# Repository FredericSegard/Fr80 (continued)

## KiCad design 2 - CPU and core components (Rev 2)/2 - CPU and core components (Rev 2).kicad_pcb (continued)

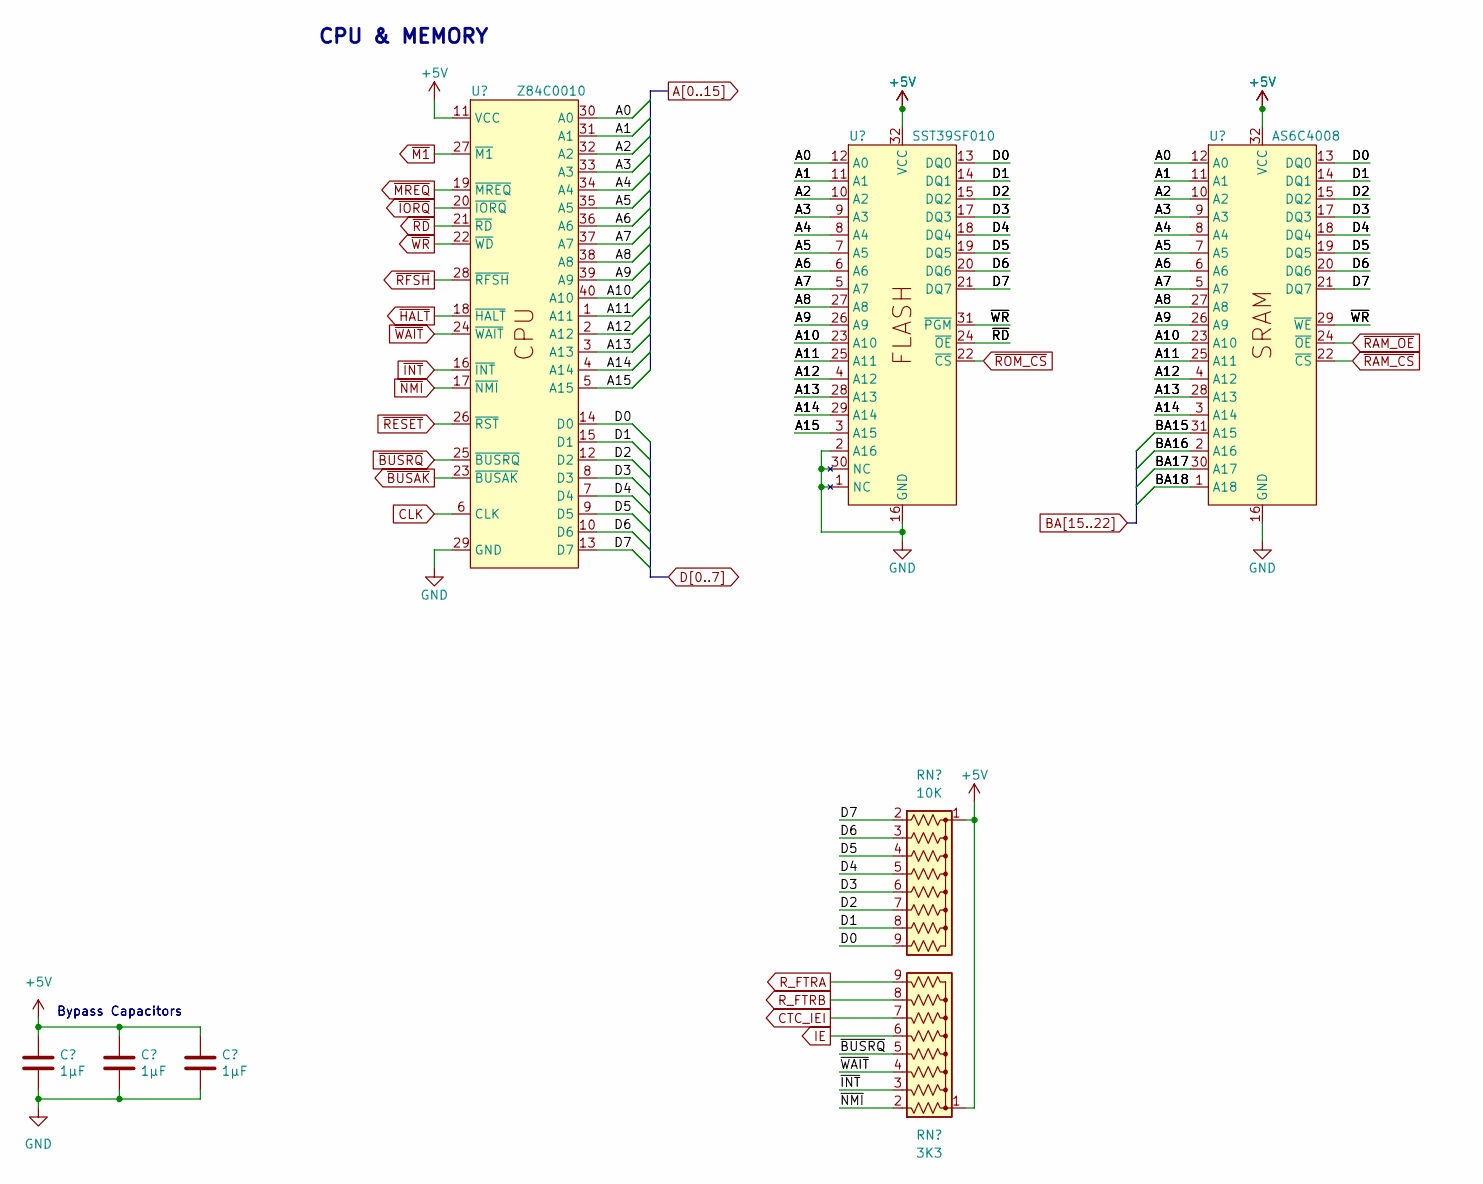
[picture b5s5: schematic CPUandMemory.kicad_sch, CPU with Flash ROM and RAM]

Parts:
C11, C12, C13: 1µF; C_Disc_D3.4mm_W2.1mm_P2.50mm
RN3: 10K; R_Array_SIP9
RN4: 3K3; R_Array_SIP9
U10: Z84C0010; DIP-40_W15.24mm_Socket
U11: SST39SF010; ZIF_Socket-32
U12: AS6C4008; DIP-32_W15.24mm_Socket

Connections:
+5V: C11.1, C12.1, C13.1, RN3.1 (common), RN4.1 (common), U10.11 (VCC), U11.32 (VCC), U12.32 (VCC); also elsewhere on the board
A0: U10.30 (A0), U11.12 (A0), U12.12 (A0); also elsewhere on the board
A1: U10.31 (A1), U11.11 (A1), U12.11 (A1); also elsewhere on the board
A2: U10.32 (A2), U11.10 (A2), U12.10 (A2); also elsewhere on the board
A3: U10.33 (A3), U11.9 (A3), U12.9 (A3); also elsewhere on the board
A4: U10.34 (A4), U11.8 (A4), U12.8 (A4); also elsewhere on the board
A5: U10.35 (A5), U11.7 (A5), U12.7 (A5); also elsewhere on the board
A6: U10.36 (A6), U11.6 (A6), U12.6 (A6); also elsewhere on the board
A7: U10.37 (A7), U11.5 (A7), U12.5 (A7); also elsewhere on the board
A8: U10.38 (A8), U11.27 (A8), U12.27 (A8); also elsewhere on the board
A9: U10.39 (A9), U11.26 (A9), U12.26 (A9); also elsewhere on the board
A10: U10.40 (A10), U11.23 (A10), U12.23 (A10); also elsewhere on the board
A11: U10.1 (A11), U11.25 (A11), U12.25 (A11); also elsewhere on the board
A12: U10.2 (A12), U11.4 (A12), U12.4 (A12); also elsewhere on the board
A13: U10.3 (A13), U11.28 (A13), U12.28 (A13); also elsewhere on the board
A14: U10.4 (A14), U11.29 (A14), U12.3 (A14); also elsewhere on the board
A15: U10.5 (A15), U11.3 (A15); also elsewhere on the board
BA15: U12.31 (A15); also elsewhere on the board
BA16: U12.2 (A16); also elsewhere on the board
BA17: U12.30 (A17); also elsewhere on the board
BA18: U12.1 (A18); also elsewhere on the board
CLK: U10.6 (CLK); also elsewhere on the board
CTC_IEI: RN4.7 (R6); also elsewhere on the board
D0: RN3.9 (R8), U10.14 (D0), U11.13 (DQ0), U12.13 (DQ0); also elsewhere on the board
D1: RN3.8 (R7), U10.15 (D1), U11.14 (DQ1), U12.14 (DQ1); also elsewhere on the board
D2: RN3.7 (R6), U10.12 (D2), U11.15 (DQ2), U12.15 (DQ2); also elsewhere on the board
D3: RN3.6 (R5), U10.8 (D3), U11.17 (DQ3), U12.17 (DQ3); also elsewhere on the board
D4: RN3.5 (R4), U10.7 (D4), U11.18 (DQ4), U12.18 (DQ4); also elsewhere on the board
D5: RN3.4 (R3), U10.9 (D5), U11.19 (DQ5), U12.19 (DQ5); also elsewhere on the board
D6: RN3.3 (R2), U10.10 (D6), U11.20 (DQ6), U12.20 (DQ6); also elsewhere on the board
D7: RN3.2 (R1), U10.13 (D7), U11.21 (DQ7), U12.21 (DQ7); also elsewhere on the board
GND: C11.2, C12.2, C13.2, U10.29 (GND), U11.1 (NC), U11.2 (A16), U11.16 (GND), U11.30 (NC), U12.16 (GND); also elsewhere on the board
IE: RN4.6 (R5); also elsewhere on the board
R_FTRA: RN4.9 (R8); also elsewhere on the board
R_FTRB: RN4.8 (R7); also elsewhere on the board
~BUSAK: U10.23 (~BUSAK); also elsewhere on the board
~BUSRQ: RN4.5 (R4), U10.25 (~BUSRQ); also elsewhere on the board
~HALT: U10.18 (~HALT); also elsewhere on the board
~INT: RN4.3 (R2), U10.16 (~INT); also elsewhere on the board
~IORQ: U10.20 (~IORQ); also elsewhere on the board
~M1: U10.27 (~M1); also elsewhere on the board
~MREQ: U10.19 (~MREQ); also elsewhere on the board
~NMI: RN4.2 (R1), U10.17 (~NMI); also elsewhere on the board
~RAM_CS: U12.22 (~CS); also elsewhere on the board
~RAM_OE: U12.24 (~OE); also elsewhere on the board
~RD: U10.21 (~RD), U11.24 (~OE); also elsewhere on the board
~RESET: U10.26 (~RST); also elsewhere on the board
~RFSH: U10.28 (~RFSH); also elsewhere on the board
~ROM_CS: U11.22 (~CS); also elsewhere on the board
~WAIT: RN4.4 (R3), U10.24 (~WAIT); also elsewhere on the board
~WR: U10.22 (~WD), U11.31 (~PGM), U12.29 (~WE); also elsewhere on the board

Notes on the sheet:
Bypass Capacitors
CPU & MEMORY

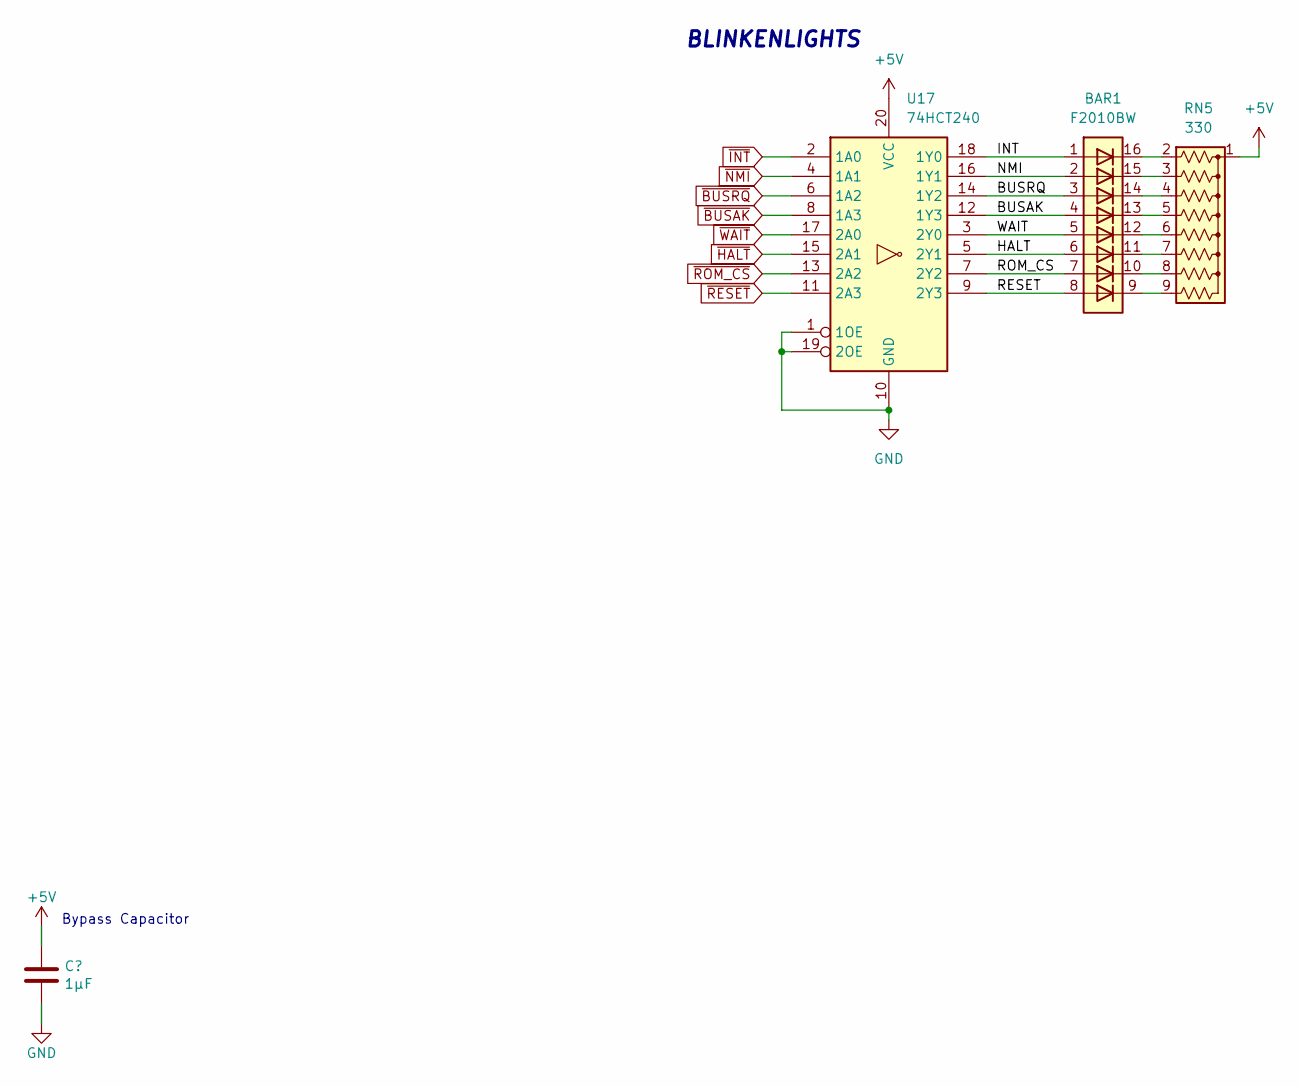
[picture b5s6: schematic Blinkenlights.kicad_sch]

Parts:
BAR1: F2010BW; BAR_GRAPH_8
C14: 1µF; C_Disc_D3.4mm_W2.1mm_P2.50mm
RN5: 330; R_Array_SIP9
U17: 74HCT240; DIP-20_W7.62mm_Socket

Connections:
+5V: C14.1, RN5.1 (common), U17.20 (VCC); also elsewhere on the board
/Blinkenlights/BUSAK: BAR1.4 (A), U17.12 (1Y3)
/Blinkenlights/BUSRQ: BAR1.3 (A), U17.14 (1Y2)
/Blinkenlights/HALT: BAR1.6 (A), U17.5 (2Y1)
/Blinkenlights/INT: BAR1.1 (A), U17.18 (1Y0)
/Blinkenlights/NMI: BAR1.2 (A), U17.16 (1Y1)
/Blinkenlights/RESET: BAR1.8 (A), U17.9 (2Y3)
/Blinkenlights/ROM_CS: BAR1.7 (A), U17.7 (2Y2)
/Blinkenlights/WAIT: BAR1.5 (A), U17.3 (2Y0)
GND: C14.2, U17.1 (1OE), U17.10 (GND), U17.19 (2OE); also elsewhere on the board
unnamed: BAR1.16 (K), RN5.2 (R1)
unnamed: BAR1.15 (K), RN5.3 (R2)
unnamed: BAR1.14 (K), RN5.4 (R3)
unnamed: BAR1.13 (K), RN5.5 (R4)
unnamed: BAR1.12 (K), RN5.6 (R5)
unnamed: BAR1.11 (K), RN5.7 (R6)
unnamed: BAR1.10 (A), RN5.8 (R7)
unnamed: BAR1.9 (A), RN5.9 (R8)
~BUSAK: U17.8 (1A3); also elsewhere on the board
~BUSRQ: U17.6 (1A2); also elsewhere on the board
~HALT: U17.15 (2A1); also elsewhere on the board
~INT: U17.2 (1A0); also elsewhere on the board
~NMI: U17.4 (1A1); also elsewhere on the board
~RESET: U17.11 (2A3); also elsewhere on the board
~ROM_CS: U17.13 (2A2); also elsewhere on the board
~WAIT: U17.17 (2A0); also elsewhere on the board

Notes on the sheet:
BLINKENLIGHTS
Bypass Capacitor

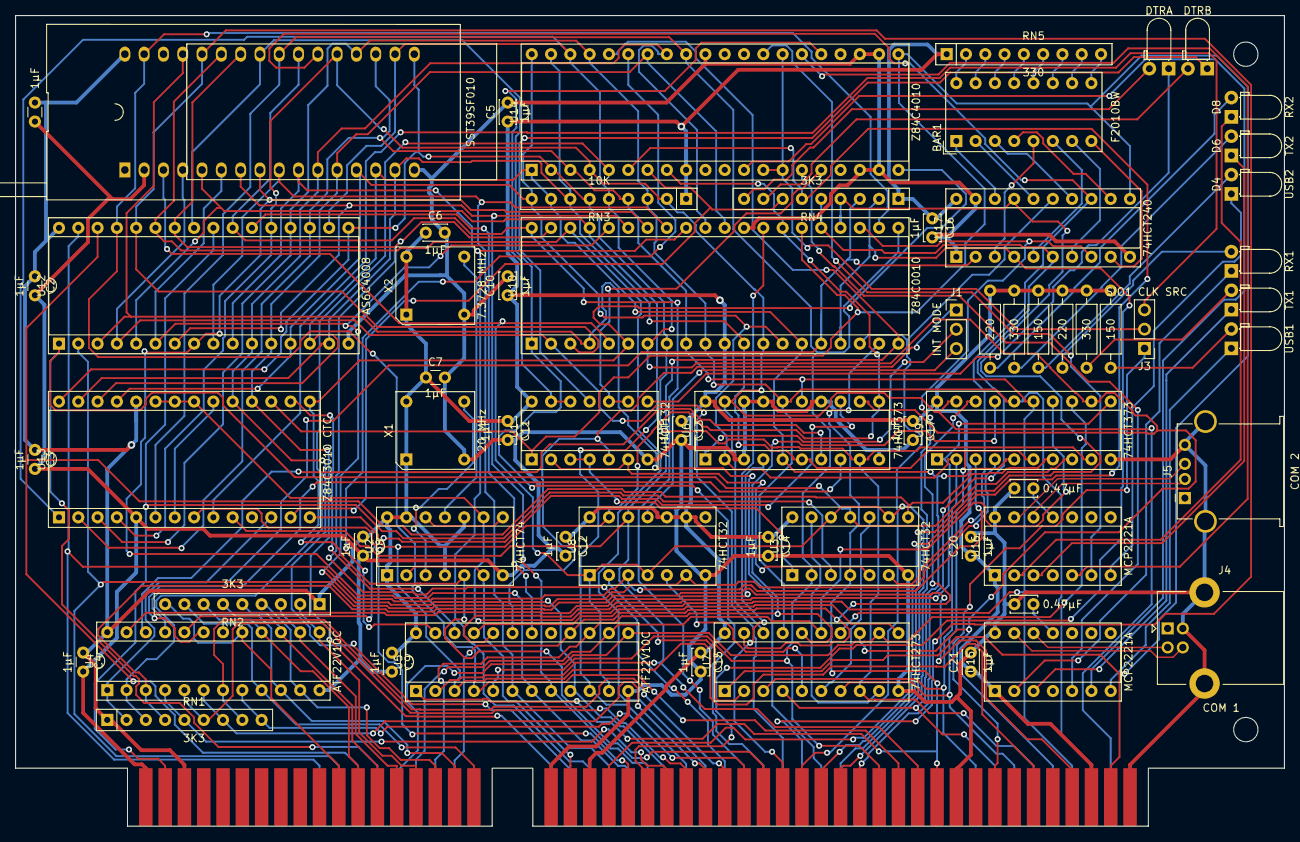
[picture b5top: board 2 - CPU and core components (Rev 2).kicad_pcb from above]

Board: 2 copper layers, 167.0 x 106.7 mm, 65 parts (0 on the bottom side), 139 nets.

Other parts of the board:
C10: 1µF; C_Disc_D3.4mm_W2.1mm_P2.50mm

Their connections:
+5V: C10.1; also elsewhere on the board
GND: C10.2; also elsewhere on the board

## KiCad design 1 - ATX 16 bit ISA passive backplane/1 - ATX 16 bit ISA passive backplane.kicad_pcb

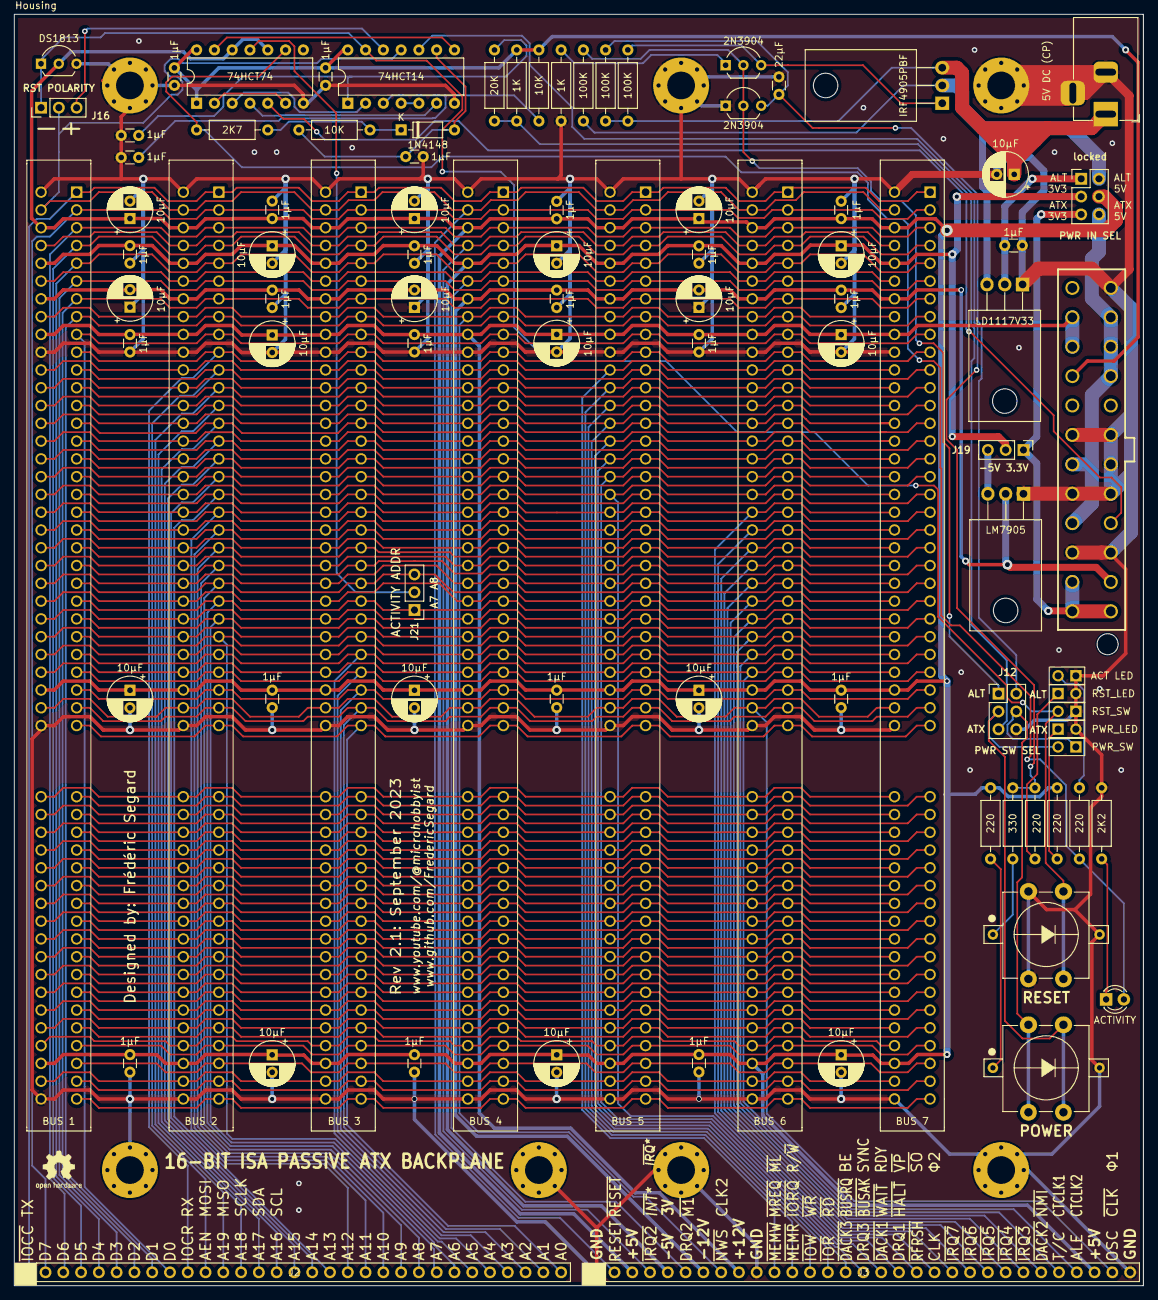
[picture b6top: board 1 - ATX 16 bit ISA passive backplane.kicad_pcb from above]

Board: 2 copper layers, 161.3 x 181.6 mm, 102 parts (1 on the bottom side), 128 nets.

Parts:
C1, C2, C3, C4, C6, C8, C9, C10, C11, C13, C14, C15, C19, C24, C29, C31, C33, C35, C37: 10µF; CP_Radial_D6.3mm_P2.50mm
C5, C7, C12, C16, C17, C18, C20, C21, C22, C23, C25, C26, C27, C28, C30, C32, C34, C36, C38, C39, C42, C44, C45, C46: 1µF; C_Disc_D3.0mm_W1.6mm_P2.50mm
C41: 22µF; C_Disc_D3.0mm_W1.6mm_P2.50mm
D2: 1N4148; D_DO-35_SOD27_P7.62mm_Horizontal
D3: ACTIVITY; LED_D3.0mm
H1, H2, H3, H4, H5, H6, H7: MH; MountingHole_M3.96_Pad_Via_ATX
J1: BUS 1; ISA_Connector_98
J2: A: Component Side; PinHeader_1x31_P2.54mm_Vertical
J3: B: Back Side; PinHeader_1x31_P2.54mm_Vertical
J4: BUS 2; ISA_Connector_98
J5: BUS 3; ISA_Connector_98
J6: BUS 4; ISA_Connector_98
J7: BUS 5; ISA_Connector_98
J8: BUS 6; ISA_Connector_98
J9: BUS 7; ISA_Connector_98
J10: ATX POWER; ATX_PSU_CONN
J12: PWR SW SEL; PinHeader_2x03_P2.54mm_Vertical
J13: PWR_LED; PinHeader_1x2_Vertical (Modified)
J14: PWR_SW; PinHeader_1x2_Vertical (Modified)
J15: 5V DC (CP); BarrelJack_Horizontal
J16: RST POLARITY; PinHeader_1x03_P2.54mm_Vertical
J17: RST_LED; PinHeader_1x2_Vertical (Modified)
J18: RST_SW; PinHeader_1x2_Vertical (Modified)
J19: 3V/-5V; PinHeader_1x03_P2.54mm_Vertical
J20: ACT LED; PinHeader_1x2_Vertical (Modified)
J21: ACTIVITY ADDR; PinHeader_1x03_P2.54mm_Vertical
LOGO1, LOGO2: Logo_Open_Hardware_Small; OSHW-Logo2_7.3x6mm_SilkScreen
N1: Housing; ATX_Backplane
Q1: IRF4905PBF; TO-220-3_Horizontal_TabDown
Q2, Q3: 2N3904; TO-92_Inline_Wide
R1, R2, R11, R17: 220; R_Axial_DIN0207_L6.3mm_D2.5mm_P10.16mm_Horizontal
R3, R6, R7: 100K; R_Axial_DIN0207_L6.3mm_D2.5mm_P10.16mm_Horizontal
R4, R14: 10K; R_Axial_DIN0207_L6.3mm_D2.5mm_P10.16mm_Horizontal
R5, R8: 1K; R_Axial_DIN0207_L6.3mm_D2.5mm_P10.16mm_Horizontal
R9: 20K; R_Axial_DIN0207_L6.3mm_D2.5mm_P10.16mm_Horizontal
R10: 330; R_Axial_DIN0207_L6.3mm_D2.5mm_P10.16mm_Horizontal
R15: 2K7; R_Axial_DIN0207_L6.3mm_D2.5mm_P10.16mm_Horizontal
R16: 2K2; R_Axial_DIN0207_L6.3mm_D2.5mm_P10.16mm_Horizontal
RS1: DS1813; TO-92L_Inline_Wide
SW1: POWER; Pushbutton_12mm_LED
SW2: RESET; Pushbutton_12mm_LED
U1: 74HCT14; DIP-14_W7.62mm
U2: LD1117V33; TO-220-3_Horizontal_TabDown
U3: 74HCT74; DIP-14_W7.62mm
U4: LM7905; TO-220-3_Horizontal_TabDown
locked: PWR IN SEL; PinHeader_2x03_P2.54mm_Vertical

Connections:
+3V3: C4.1, C5.1, C6.1, C7.1, C11.1, C12.1, J1.36 (B5), J3.5, J4.36 (B5), J5.36 (B5), J6.36 (B5), J7.36 (B5), J8.36 (B5), J9.36 (B5), J19.2, locked.3
+5V: C1.1, C2.1, C3.1, C8.1, C9.1, C10.1, C13.1, C14.1, C15.1, C16.1, C17.1, C18.1, C21.1, C22.1, C23.1, C26.1, C27.1, C28.1, J1.34 (B3), J1.60 (B29), J1.96 (D16), J3.3, J3.29, J4.34 (B3), J4.60 (B29), J4.96 (D16), J5.34 (B3), J5.60 (B29), J5.96 (D16), J6.34 (B3), J6.60 (B29), J6.96 (D16), J7.34 (B3), J7.60 (B29), J7.96 (D16), J8.34 (B3), J8.60 (B29), J8.96 (D16), J9.34 (B3), J9.60 (B29), J9.96 (D16), R1.2, R2.2, RS1.2 (VCC), U3.10 (~S), U3.12 (D), locked.4
+12V: C19.1, C20.1, C24.1, C25.1, C29.1, C30.1, J1.40 (B9), J3.9, J4.40 (B9), J5.40 (B9), J6.40 (B9), J7.40 (B9), J8.40 (B9), J9.40 (B9), J10.10 (+12V), J10.11 (+12V)
-12V: C31.2, C32.1, C33.2, C34.1, C35.2, C36.1, J1.38 (B7), J3.7, J4.38 (B7), J5.38 (B7), J6.38 (B7), J7.38 (B7), J8.38 (B7), J9.38 (B7), J10.14 (-12V), U4.2 (VI)
/A0: J1.31 (A31), J2.31, J4.31 (A31), J5.31 (A31), J6.31 (A31), J7.31 (A31), J8.31 (A31), J9.31 (A31)
/A1: J1.30 (A30), J2.30, J4.30 (A30), J5.30 (A30), J6.30 (A30), J7.30 (A30), J8.30 (A30), J9.30 (A30)
/A2: J1.29 (A29), J2.29, J4.29 (A29), J5.29 (A29), J6.29 (A29), J7.29 (A29), J8.29 (A29), J9.29 (A29)
/A3: J1.28 (A28), J2.28, J4.28 (A28), J5.28 (A28), J6.28 (A28), J7.28 (A28), J8.28 (A28), J9.28 (A28)
/A4: J1.27 (A27), J2.27, J4.27 (A27), J5.27 (A27), J6.27 (A27), J7.27 (A27), J8.27 (A27), J9.27 (A27)
/A5: J1.26 (A26), J2.26, J4.26 (A26), J5.26 (A26), J6.26 (A26), J7.26 (A26), J8.26 (A26), J9.26 (A26)
/A6: J1.25 (A25), J2.25, J4.25 (A25), J5.25 (A25), J6.25 (A25), J7.25 (A25), J8.25 (A25), J9.25 (A25)
/A7: J1.24 (A24), J2.24, J4.24 (A24), J5.24 (A24), J6.24 (A24), J7.24 (A24), J8.24 (A24), J9.24 (A24), J21.1
/A8: J1.23 (A23), J2.23, J4.23 (A23), J5.23 (A23), J6.23 (A23), J7.23 (A23), J8.23 (A23), J9.23 (A23), J21.3
/A9: J1.22 (A22), J2.22, J4.22 (A22), J5.22 (A22), J6.22 (A22), J7.22 (A22), J8.22 (A22), J9.22 (A22)
/A10: J1.21 (A21), J2.21, J4.21 (A21), J5.21 (A21), J6.21 (A21), J7.21 (A21), J8.21 (A21), J9.21 (A21)
/A11: J1.20 (A20), J2.20, J4.20 (A20), J5.20 (A20), J6.20 (A20), J7.20 (A20), J8.20 (A20), J9.20 (A20)
/A12: J1.19 (A19), J2.19, J4.19 (A19), J5.19 (A19), J6.19 (A19), J7.19 (A19), J8.19 (A19), J9.19 (A19)
/A13: J1.18 (A18), J2.18, J4.18 (A18), J5.18 (A18), J6.18 (A18), J7.18 (A18), J8.18 (A18), J9.18 (A18)
/A14: J1.17 (A17), J2.17, J4.17 (A17), J5.17 (A17), J6.17 (A17), J7.17 (A17), J8.17 (A17), J9.17 (A17)
/A15: J1.16 (A16), J2.16, J4.16 (A16), J5.16 (A16), J6.16 (A16), J7.16 (A16), J8.16 (A16), J9.16 (A16)
/A16: J1.71 (C9), J4.71 (C9), J5.71 (C9), J6.71 (C9), J7.71 (C9), J8.71 (C9), J9.71 (C9)
/A17: J1.70 (C8), J4.70 (C8), J5.70 (C8), J6.70 (C8), J7.70 (C8), J8.70 (C8), J9.70 (C8)
/A18: J1.69 (C7), J4.69 (C7), J5.69 (C7), J6.69 (C7), J7.69 (C7), J8.69 (C7), J9.69 (C7)
/A19: J1.68 (C6), J4.68 (C6), J5.68 (C6), J6.68 (C6), J7.68 (C6), J8.68 (C6), J9.68 (C6)
/A20: J1.67 (C5), J4.67 (C5), J5.67 (C5), J6.67 (C5), J7.67 (C5), J8.67 (C5), J9.67 (C5)
/A21: J1.66 (C4), J4.66 (C4), J5.66 (C4), J6.66 (C4), J7.66 (C4), J8.66 (C4), J9.66 (C4)
/A22: J1.65 (C3), J4.65 (C3), J5.65 (C3), J6.65 (C3), J7.65 (C3), J8.65 (C3), J9.65 (C3)
/A23: J1.64 (C2), J4.64 (C2), J5.64 (C2), J6.64 (C2), J7.64 (C2), J8.64 (C2), J9.64 (C2)
/CLK: J1.51 (B20), J3.20, J4.51 (B20), J5.51 (B20), J6.51 (B20), J7.51 (B20), J8.51 (B20), J9.51 (B20)
/CLK2: J1.39 (B8), J3.8, J4.39 (B8), J5.39 (B8), J6.39 (B8), J7.39 (B8), J8.39 (B8), J9.39 (B8)
/CTCLK1: J1.58 (B27), J3.27, J4.58 (B27), J5.58 (B27), J6.58 (B27), J7.58 (B27), J8.58 (B27), J9.58 (B27)
/CTCLK2: J1.59 (B28), J3.28, J4.59 (B28), J5.59 (B28), J6.59 (B28), J7.59 (B28), J8.59 (B28), J9.59 (B28)
/D0: J1.9 (A9), J2.9, J4.9 (A9), J5.9 (A9), J6.9 (A9), J7.9 (A9), J8.9 (A9), J9.9 (A9)
/D1: J1.8 (A8), J2.8, J4.8 (A8), J5.8 (A8), J6.8 (A8), J7.8 (A8), J8.8 (A8), J9.8 (A8)
/D2: J1.7 (A7), J2.7, J4.7 (A7), J5.7 (A7), J6.7 (A7), J7.7 (A7), J8.7 (A7), J9.7 (A7)
/D3: J1.6 (A6), J2.6, J4.6 (A6), J5.6 (A6), J6.6 (A6), J7.6 (A6), J8.6 (A6), J9.6 (A6)
/D4: J1.5 (A5), J2.5, J4.5 (A5), J5.5 (A5), J6.5 (A5), J7.5 (A5), J8.5 (A5), J9.5 (A5)
/D5: J1.4 (A4), J2.4, J4.4 (A4), J5.4 (A4), J6.4 (A4), J7.4 (A4), J8.4 (A4), J9.4 (A4)
/D6: J1.3 (A3), J2.3, J4.3 (A3), J5.3 (A3), J6.3 (A3), J7.3 (A3), J8.3 (A3), J9.3 (A3)
/D7: J1.2 (A2), J2.2, J4.2 (A2), J5.2 (A2), J6.2 (A2), J7.2 (A2), J8.2 (A2), J9.2 (A2)
/D8: J1.73 (C11), J4.73 (C11), J5.73 (C11), J6.73 (C11), J7.73 (C11), J8.73 (C11), J9.73 (C11)
/D9: J1.74 (C12), J4.74 (C12), J5.74 (C12), J6.74 (C12), J7.74 (C12), J8.74 (C12), J9.74 (C12)
/D10: J1.75 (C13), J4.75 (C13), J5.75 (C13), J6.75 (C13), J7.75 (C13), J8.75 (C13), J9.75 (C13)
/D11: J1.76 (C14), J4.76 (C14), J5.76 (C14), J6.76 (C14), J7.76 (C14), J8.76 (C14), J9.76 (C14)
/D12: J1.77 (C15), J4.77 (C15), J5.77 (C15), J6.77 (C15), J7.77 (C15), J8.77 (C15), J9.77 (C15)
/D13: J1.78 (C16), J4.78 (C16), J5.78 (C16), J6.78 (C16), J7.78 (C16), J8.78 (C16), J9.78 (C16)
/D14: J1.79 (C17), J4.79 (C17), J5.79 (C17), J6.79 (C17), J7.79 (C17), J8.79 (C17), J9.79 (C17)
/D15: J1.80 (C18), J4.80 (C18), J5.80 (C18), J6.80 (C18), J7.80 (C18), J8.80 (C18), J9.80 (C18)
/MISO: J1.12 (A12), J2.12, J4.12 (A12), J5.12 (A12), J6.12 (A12), J7.12 (A12), J8.12 (A12), J9.12 (A12)
/MOSI: J1.11 (A11), J2.11, J4.11 (A11), J5.11 (A11), J6.11 (A11), J7.11 (A11), J8.11 (A11), J9.11 (A11)
/Power/ALT1: J12.1, Q2.2 (B), Q3.2 (B), R6.1
/Power/ALT2: C41.1, J12.2, Q3.3 (C), R7.1
/Power/ALT_3V3: C42.1, U2.2 (VO), locked.1
/Power/ALT_5V: Q1.2 (D), R6.2, U2.3 (VI), locked.2
/Power/ATX: J12.5, R8.2, R9.1
/Power/ATX_3V3: J10.1 (+3.3V), J10.2 (+3.3V), J10.13 (+3.3V), J19.1, locked.5
/Power/ATX_5V: J10.4 (+5V), J10.6 (+5V), J10.21 (+5V), J10.22 (+5V), J10.23 (+5V), locked.6
/Power/ATX_-5V: J19.3, U4.3 (VO)
/Power/Vin: C37.1, J15.1, Q1.3 (S), R3.2, R7.2
/Power/~PS_ON: J10.16 (~PS_ON), U3.5 (Q)
/Power/~PWR_UP: U1.6, U3.4 (~S)
/RX: J1.10 (A10), J2.10, J4.10 (A10), J5.10 (A10), J6.10 (A10), J7.10 (A10), J8.10 (A10), J9.10 (A10)
/RX2: J1.72 (C10), J4.72 (C10), J5.72 (C10), J6.72 (C10), J7.72 (C10), J8.72 (C10), J9.72 (C10)
/Reset & LEDs/+RST: J16.3, U1.12
/Reset & LEDs/-RST: J16.1, J18.2, RS1.1 (~RESET), SW2.2, U1.13
/SCL: J1.15 (A15), J2.15, J4.15 (A15), J5.15 (A15), J6.15 (A15), J7.15 (A15), J8.15 (A15), J9.15 (A15)
/SCLK: J1.13 (A13), J2.13, J4.13 (A13), J5.13 (A13), J6.13 (A13), J7.13 (A13), J8.13 (A13), J9.13 (A13)
/SDA: J1.14 (A14), J2.14, J4.14 (A14), J5.14 (A14), J6.14 (A14), J7.14 (A14), J8.14 (A14), J9.14 (A14)
/TX: J1.1 (A1), J2.1, J4.1 (A1), J5.1 (A1), J6.1 (A1), J7.1 (A1), J8.1 (A1), J9.1 (A1)
/TX2: J1.63 (C1), J4.63 (C1), J5.63 (C1), J6.63 (C1), J7.63 (C1), J8.63 (C1), J9.63 (C1)
/USR1: J1.89 (D9), J4.89 (D9), J5.89 (D9), J6.89 (D9), J7.89 (D9), J8.89 (D9), J9.89 (D9)
/USR2: J1.90 (D10), J4.90 (D10), J5.90 (D10), J6.90 (D10), J7.90 (D10), J8.90 (D10), J9.90 (D10)
/USR3: J1.91 (D11), J4.91 (D11), J5.91 (D11), J6.91 (D11), J7.91 (D11), J8.91 (D11), J9.91 (D11)
/USR4: J1.92 (D12), J4.92 (D12), J5.92 (D12), J6.92 (D12), J7.92 (D12), J8.92 (D12), J9.92 (D12)
/USR5: J1.93 (D13), J4.93 (D13), J5.93 (D13), J6.93 (D13), J7.93 (D13), J8.93 (D13), J9.93 (D13)
/USR6: J1.94 (D14), J4.94 (D14), J5.94 (D14), J6.94 (D14), J7.94 (D14), J8.94 (D14), J9.94 (D14)
/USR7: J1.95 (D15), J4.95 (D15), J5.95 (D15), J6.95 (D15), J7.95 (D15), J8.95 (D15), J9.95 (D15)
/USR8: J1.97 (D17), J4.97 (D17), J5.97 (D17), J6.97 (D17), J7.97 (D17), J8.97 (D17), J9.97 (D17)
/~BUSAK: J1.47 (B16), J3.16, J4.47 (B16), J5.47 (B16), J6.47 (B16), J7.47 (B16), J8.47 (B16), J9.47 (B16)
/~BUSRQ: J1.46 (B15), J3.15, J4.46 (B15), J5.46 (B15), J6.46 (B15), J7.46 (B15), J8.46 (B15), J9.46 (B15)
/~CLK: J1.61 (B30), J3.30, J4.61 (B30), J5.61 (B30), J6.61 (B30), J7.61 (B30), J8.61 (B30), J9.61 (B30)
/~HALT: J1.49 (B18), J3.18, J4.49 (B18), J5.49 (B18), J6.49 (B18), J7.49 (B18), J8.49 (B18), J9.49 (B18)
/~IORQ: J1.43 (B12), J3.12, J4.43 (B12), J5.43 (B12), J6.43 (B12), J7.43 (B12), J8.43 (B12), J9.43 (B12)
/~IRQ2: J1.35 (B4), J3.4, J4.35 (B4), J5.35 (B4), J6.35 (B4), J7.35 (B4), J8.35 (B4), J9.35 (B4)
/~IRQ3: J1.56 (B25), J3.25, J4.56 (B25), J5.56 (B25), J6.56 (B25), J7.56 (B25), J8.56 (B25), J9.56 (B25)
/~IRQ4: J1.55 (B24), J3.24, J4.55 (B24), J5.55 (B24), J6.55 (B24), J7.55 (B24), J8.55 (B24), J9.55 (B24)
/~IRQ5: J1.54 (B23), J3.23, J4.54 (B23), J5.54 (B23), J6.54 (B23), J7.54 (B23), J8.54 (B23), J9.54 (B23)
/~IRQ6: J1.53 (B22), J3.22, J4.53 (B22), J5.53 (B22), J6.53 (B22), J7.53 (B22), J8.53 (B22), J9.53 (B22)
/~IRQ7: J1.52 (B21), J3.21, J4.52 (B21), J5.52 (B21), J6.52 (B21), J7.52 (B21), J8.52 (B21), J9.52 (B21)
/~IRQ8: J1.81 (D1), J4.81 (D1), J5.81 (D1), J6.81 (D1), J7.81 (D1), J8.81 (D1), J9.81 (D1)
/~IRQ9: J1.82 (D2), J4.82 (D2), J5.82 (D2), J6.82 (D2), J7.82 (D2), J8.82 (D2), J9.82 (D2)
/~IRQ10: J1.83 (D3), J4.83 (D3), J5.83 (D3), J6.83 (D3), J7.83 (D3), J8.83 (D3), J9.83 (D3)
/~IRQ11: J1.84 (D4), J4.84 (D4), J5.84 (D4), J6.84 (D4), J7.84 (D4), J8.84 (D4), J9.84 (D4)
/~IRQ12: J1.85 (D5), J4.85 (D5), J5.85 (D5), J6.85 (D5), J7.85 (D5), J8.85 (D5), J9.85 (D5)
/~IRQ13: J1.86 (D6), J4.86 (D6), J5.86 (D6), J6.86 (D6), J7.86 (D6), J8.86 (D6), J9.86 (D6)
/~IRQ14: J1.87 (D7), J4.87 (D7), J5.87 (D7), J6.87 (D7), J7.87 (D7), J8.87 (D7), J9.87 (D7)
/~IRQ15: J1.88 (D8), J4.88 (D8), J5.88 (D8), J6.88 (D8), J7.88 (D8), J8.88 (D8), J9.88 (D8)
/~M1: J1.37 (B6), J3.6, J4.37 (B6), J5.37 (B6), J6.37 (B6), J7.37 (B6), J8.37 (B6), J9.37 (B6)
/~MREQ: J1.42 (B11), J3.11, J4.42 (B11), J5.42 (B11), J6.42 (B11), J7.42 (B11), J8.42 (B11), J9.42 (B11)
/~NMI: J1.57 (B26), J3.26, J4.57 (B26), J5.57 (B26), J6.57 (B26), J7.57 (B26), J8.57 (B26), J9.57 (B26)
/~RD: J1.45 (B14), J3.14, J4.45 (B14), J5.45 (B14), J6.45 (B14), J7.45 (B14), J8.45 (B14), J9.45 (B14)
/~RESET: J1.33 (B2), J3.2, J4.33 (B2), J5.33 (B2), J6.33 (B2), J7.33 (B2), J8.33 (B2), J9.33 (B2), J16.2, U1.11
/~RFSH: J1.50 (B19), J3.19, J4.50 (B19), J5.50 (B19), J6.50 (B19), J7.50 (B19), J8.50 (B19), J9.50 (B19)
/~WAIT: J1.48 (B17), J3.17, J4.48 (B17), J5.48 (B17), J6.48 (B17), J7.48 (B17), J8.48 (B17), J9.48 (B17)
/~WR: J1.44 (B13), J3.13, J4.44 (B13), J5.44 (B13), J6.44 (B13), J7.44 (B13), J8.44 (B13), J9.44 (B13)
GND: C1.2, C2.2, C3.2, C4.2, C5.2, C6.2, C7.2, C8.2, C9.2, C10.2, C11.2, C12.2, C13.2, C14.2, C15.2, C16.2, C17.2, C18.2, C19.2, C20.2, C21.2, C22.2, C23.2, C24.2, C25.2, C26.2, C27.2, C28.2, C29.2, C30.2, C31.1, C32.2, C33.1, C34.2, C35.1, C36.2, C37.2, C38.2, C39.2, C41.2, C42.2, C44.2, C45.2, C46.2, H1.1, H2.1, H3.1, H4.1, H5.1, H6.1, H7.1, J1.32 (B1), J1.41 (B10), J1.62 (B31), J1.98 (D18), J3.1, J3.10, J3.31, J4.32 (B1), J4.41 (B10), J4.62 (B31), J4.98 (D18), J5.32 (B1), J5.41 (B10), J5.62 (B31), J5.98 (D18), J6.32 (B1), J6.41 (B10), J6.62 (B31), J6.98 (D18), J7.32 (B1), J7.41 (B10), J7.62 (B31), J7.98 (D18), J8.32 (B1), J8.41 (B10), J8.62 (B31), J8.98 (D18), J9.32 (B1), J9.41 (B10), J9.62 (B31), J9.98 (D18), J10.3 (GND), J10.5 (GND), J10.7 (GND), J10.15 (GND), J10.17 (GND), J10.18 (GND), J10.19 (GND), J10.24 (GND), J12.6, J13.2, J15.2, J15.3, J17.2, J18.1, J20.1, Q3.1 (E), R5.1, R16.2, RS1.3 (GND), SW1.3 (K), SW2.1, SW2.3 (K), U1.7 (GND), U2.1 (GND), U3.7 (GND), U4.1 (GND)
unnamed: C38.1, R4.2, U1.3
unnamed: C39.1, R9.2, U1.1
unnamed: C46.1, D2.2 (A), R14.2, U1.9
unnamed: D2.1 (K), R14.1, R15.1
unnamed: D3.2 (A), R15.2, R17.1, U3.9 (Q)
unnamed: D3.1 (K), R16.1
unnamed: J12.3, J14.2, SW1.2
unnamed: J12.4, J14.1, SW1.1
unnamed: J13.1, R2.1
unnamed: J17.1, R11.1
unnamed: J20.2, R17.2
unnamed: J21.2, U3.11 (C)
unnamed: Q1.1 (G), Q2.3 (C), R3.1
unnamed: Q2.1 (E), R5.2
unnamed: R10.2, R11.2, U1.10
unnamed: R1.1, SW1.4 (A)
unnamed: R10.1, SW2.4 (A)
unnamed: U1.4, U1.5
unnamed: U1.2, U3.3 (C)
unnamed: U3.2 (D), U3.6 (~Q)
unnamed: U1.8, U3.13 (~R)
VCC: C44.1, C45.1, J10.9 (+5VSB), R4.1, R8.1, U1.14 (VCC), U3.1 (~R), U3.14 (VCC)

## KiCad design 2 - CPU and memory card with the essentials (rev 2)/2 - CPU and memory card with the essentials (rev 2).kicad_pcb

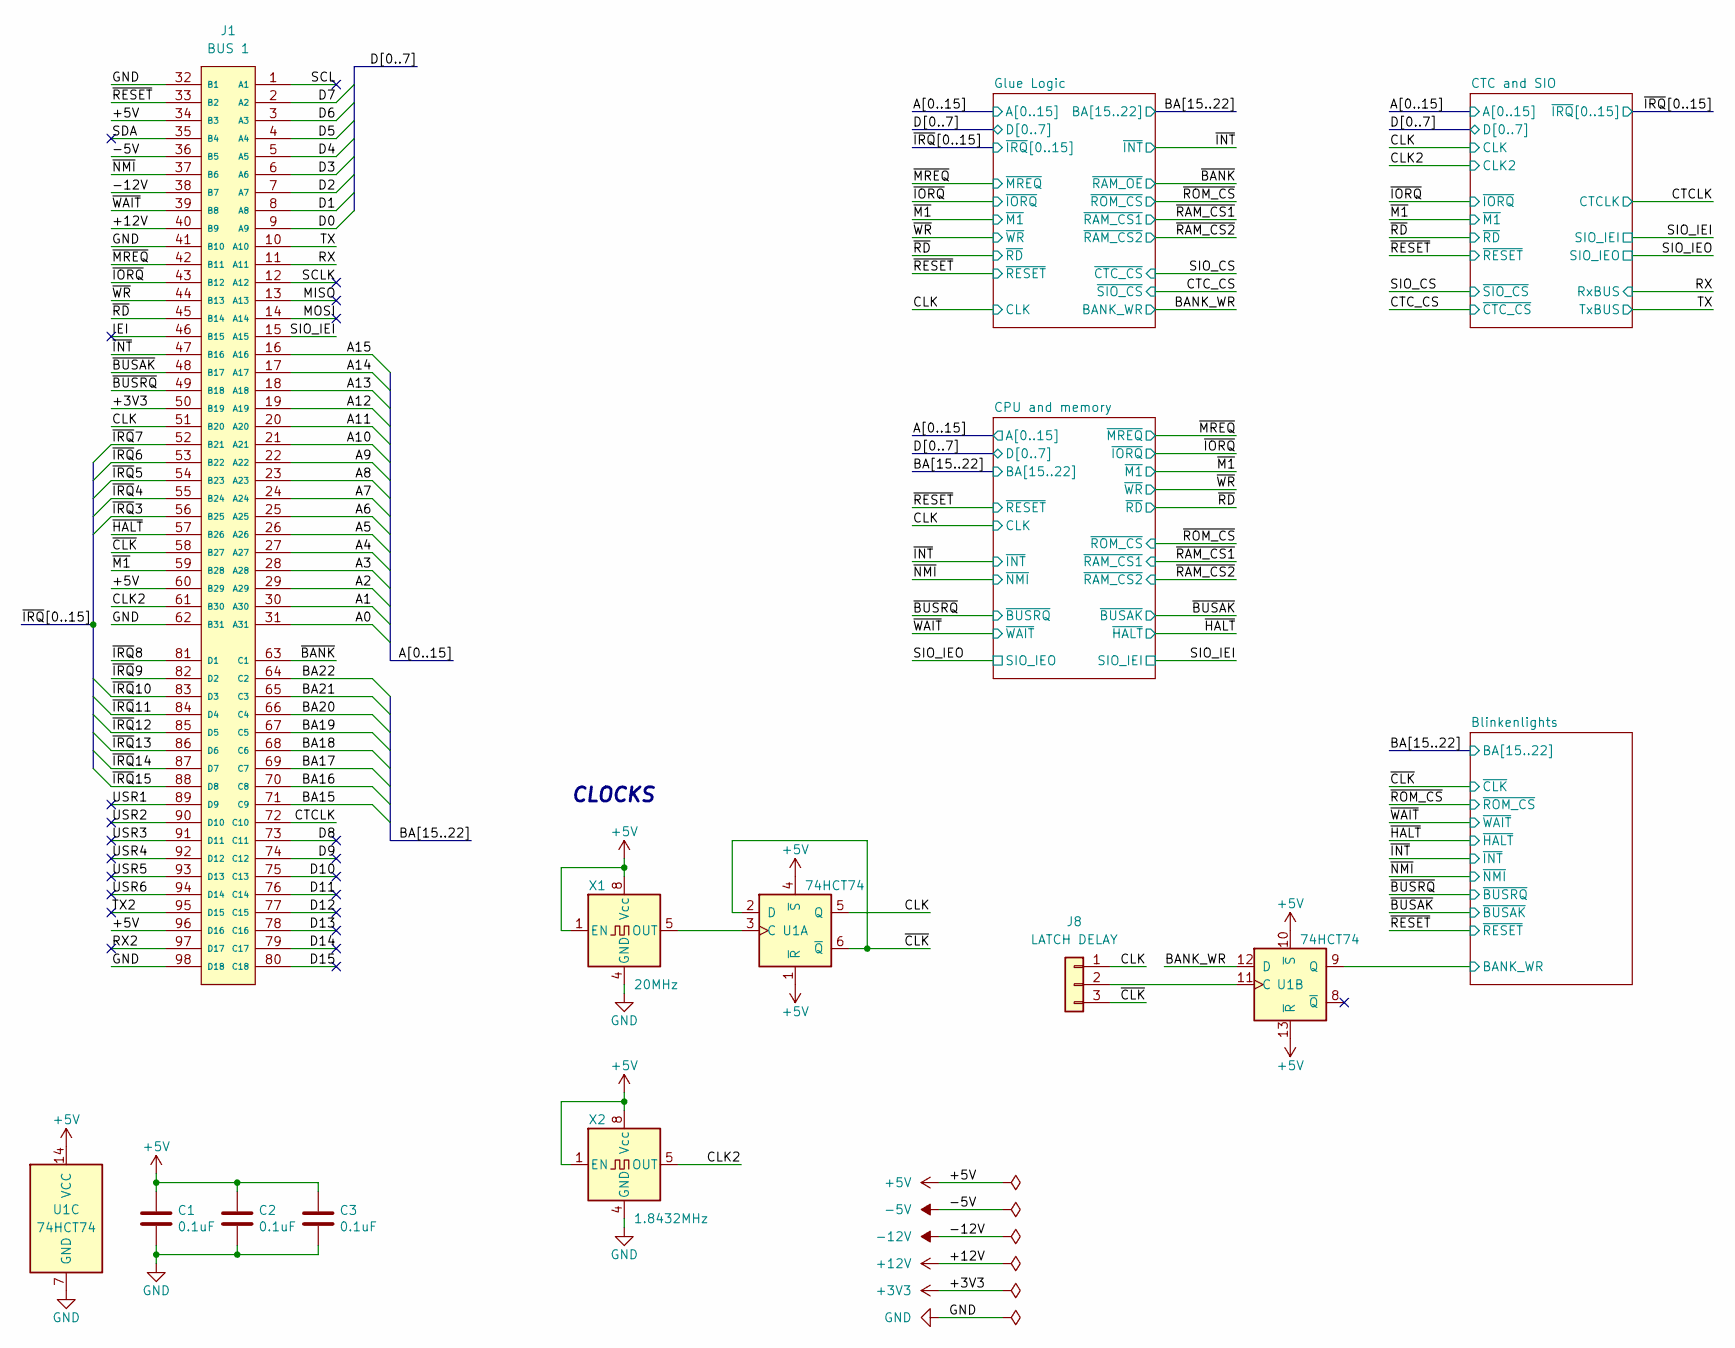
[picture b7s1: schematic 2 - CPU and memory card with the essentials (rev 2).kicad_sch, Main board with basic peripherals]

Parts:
C1, C2, C3: 0.1uF; C_Disc_D3.0mm_W2.0mm_P2.50mm
J1: BUS 1; BUS_AT v2; Mouser Part Number 571-5645169-3
J8: LATCH DELAY; PinHeader_1x03_P2.54mm_Vertical
U1: 74HCT74; DIP-14_W7.62mm_Socket
X1: 20MHz; DIP-8-4_W7.62mm_Oscillator_Socket
X2: 1.8432MHz; DIP-8-4_W7.62mm_Oscillator_Socket

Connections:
+3V3: J1.50 (B19)
+5V: C1.1, C2.1, C3.1, J1.34 (B3), J1.60 (B29), J1.96 (D16), U1.1 (~R), U1.4 (~S), U1.10 (~S), U1.13 (~R), U1.14 (VCC), X1.1 (EN), X1.8 (Vcc), X2.1 (EN), X2.8 (Vcc); also elsewhere on the board
+12V: J1.40 (B9)
-5V: J1.36 (B5)
-12V: J1.38 (B7)
/A0: J1.31 (A31); also elsewhere on the board
/A1: J1.30 (A30); also elsewhere on the board
/A2: J1.29 (A29); also elsewhere on the board
/A3: J1.28 (A28); also elsewhere on the board
/A4: J1.27 (A27); also elsewhere on the board
/A5: J1.26 (A26); also elsewhere on the board
/A6: J1.25 (A25); also elsewhere on the board
/A7: J1.24 (A24); also elsewhere on the board
/A8: J1.23 (A23); also elsewhere on the board
/A9: J1.22 (A22); also elsewhere on the board
/A10: J1.21 (A21); also elsewhere on the board
/A11: J1.20 (A20); also elsewhere on the board
/A12: J1.19 (A19); also elsewhere on the board
/A13: J1.18 (A18); also elsewhere on the board
/A14: J1.17 (A17); also elsewhere on the board
/A15: J1.16 (A16); also elsewhere on the board
/BA15: J1.71 (C9); also elsewhere on the board
/BA16: J1.70 (C8); also elsewhere on the board
/BA17: J1.69 (C7); also elsewhere on the board
/BA18: J1.68 (C6); also elsewhere on the board
/BA19: J1.67 (C5); also elsewhere on the board
/BA20: J1.66 (C4); also elsewhere on the board
/BA21: J1.65 (C3); also elsewhere on the board
/BA22: J1.64 (C2); also elsewhere on the board
/BANK_WR: U1.12 (D); also elsewhere on the board
/Blinkenlights/BANK_WR: U1.9 (Q); also elsewhere on the board
/CLK: J1.51 (B20), J8.1, U1.5 (Q); also elsewhere on the board
/CLK2: J1.61 (B30), X2.5 (OUT); also elsewhere on the board
/CTCLK: J1.72 (C10); also elsewhere on the board
/D0: J1.9 (A9); also elsewhere on the board
/D1: J1.8 (A8); also elsewhere on the board
/D2: J1.7 (A7); also elsewhere on the board
/D3: J1.6 (A6); also elsewhere on the board
/D4: J1.5 (A5); also elsewhere on the board
/D5: J1.4 (A4); also elsewhere on the board
/D6: J1.3 (A3); also elsewhere on the board
/D7: J1.2 (A2); also elsewhere on the board
/D8: J1.73 (C11)
/D9: J1.74 (C12)
/D10: J1.75 (C13)
/D11: J1.76 (C14)
/D12: J1.77 (C15)
/D13: J1.78 (C16)
/D14: J1.79 (C17)
/D15: J1.80 (C18)
/IEI: J1.46 (B15)
/MISO: J1.13 (A13)
/MOSI: J1.14 (A14)
/RX: J1.11 (A11); also elsewhere on the board
/RX2: J1.97 (D17)
/SCL: J1.1 (A1)
/SCLK: J1.12 (A12)
/SDA: J1.35 (B4)
/SIO_IEI: J1.15 (A15); also elsewhere on the board
/TX: J1.10 (A10); also elsewhere on the board
/TX2: J1.95 (D15)
/USR1: J1.89 (D9)
/USR2: J1.90 (D10)
/USR3: J1.91 (D11)
/USR4: J1.92 (D12)
/USR5: J1.93 (D13)
/USR6: J1.94 (D14)
/~BANK: J1.63 (C1); also elsewhere on the board
/~BUSAK: J1.48 (B17); also elsewhere on the board
/~BUSRQ: J1.49 (B18); also elsewhere on the board
/~CLK: J1.58 (B27), J8.3, U1.2 (D), U1.6 (~Q); also elsewhere on the board
/~HALT: J1.57 (B26); also elsewhere on the board
/~INT: J1.47 (B16); also elsewhere on the board
/~IORQ: J1.43 (B12); also elsewhere on the board
/~IRQ3: J1.56 (B25); also elsewhere on the board
/~IRQ4: J1.55 (B24); also elsewhere on the board
/~IRQ5: J1.54 (B23); also elsewhere on the board
/~IRQ6: J1.53 (B22); also elsewhere on the board
/~IRQ7: J1.52 (B21); also elsewhere on the board
/~IRQ8: J1.81 (D1); also elsewhere on the board
/~IRQ9: J1.82 (D2); also elsewhere on the board
/~IRQ10: J1.83 (D3); also elsewhere on the board
/~IRQ11: J1.84 (D4); also elsewhere on the board
/~IRQ12: J1.85 (D5); also elsewhere on the board
/~IRQ13: J1.86 (D6); also elsewhere on the board
/~IRQ14: J1.87 (D7); also elsewhere on the board
/~IRQ15: J1.88 (D8); also elsewhere on the board
/~M1: J1.59 (B28); also elsewhere on the board
/~MREQ: J1.42 (B11); also elsewhere on the board
/~NMI: J1.37 (B6); also elsewhere on the board
/~RD: J1.45 (B14); also elsewhere on the board
/~RESET: J1.33 (B2); also elsewhere on the board
/~WAIT: J1.39 (B8); also elsewhere on the board
/~WR: J1.44 (B13); also elsewhere on the board
GND: C1.2, C2.2, C3.2, J1.32 (B1), J1.41 (B10), J1.62 (B31), J1.98 (D18), U1.7 (GND), X1.4 (GND), X2.4 (GND); also elsewhere on the board
unnamed: J8.2, U1.11 (C)
unnamed: U1.3 (C), X1.5 (OUT)

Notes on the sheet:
CLOCKS
